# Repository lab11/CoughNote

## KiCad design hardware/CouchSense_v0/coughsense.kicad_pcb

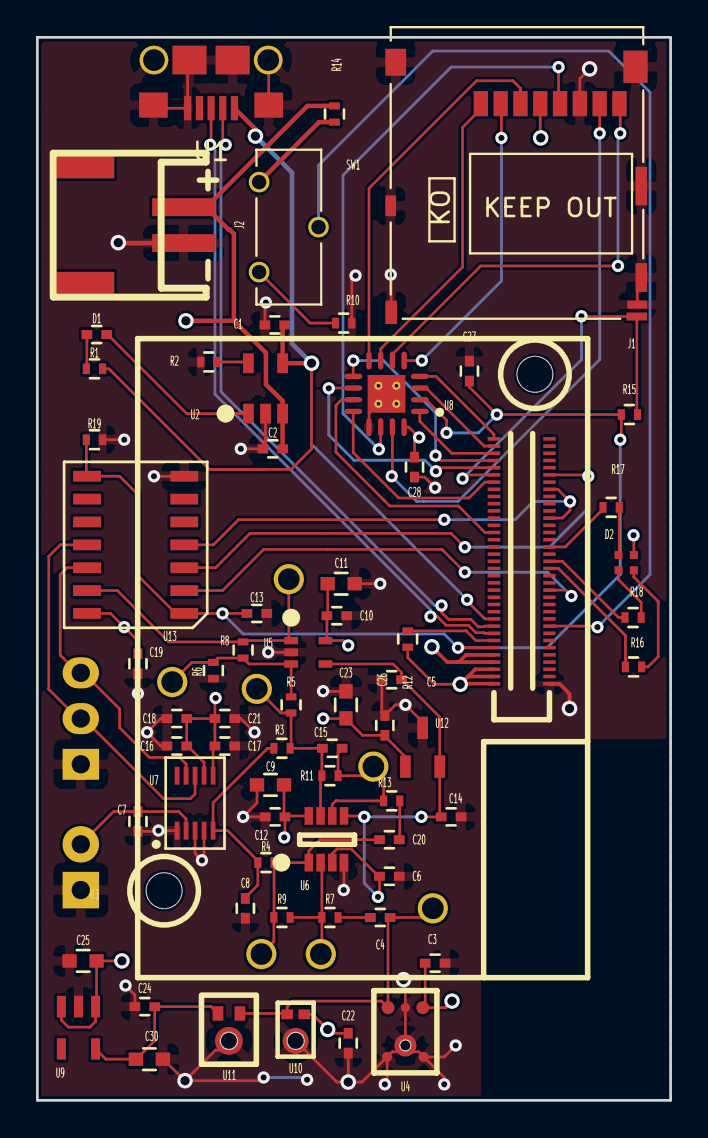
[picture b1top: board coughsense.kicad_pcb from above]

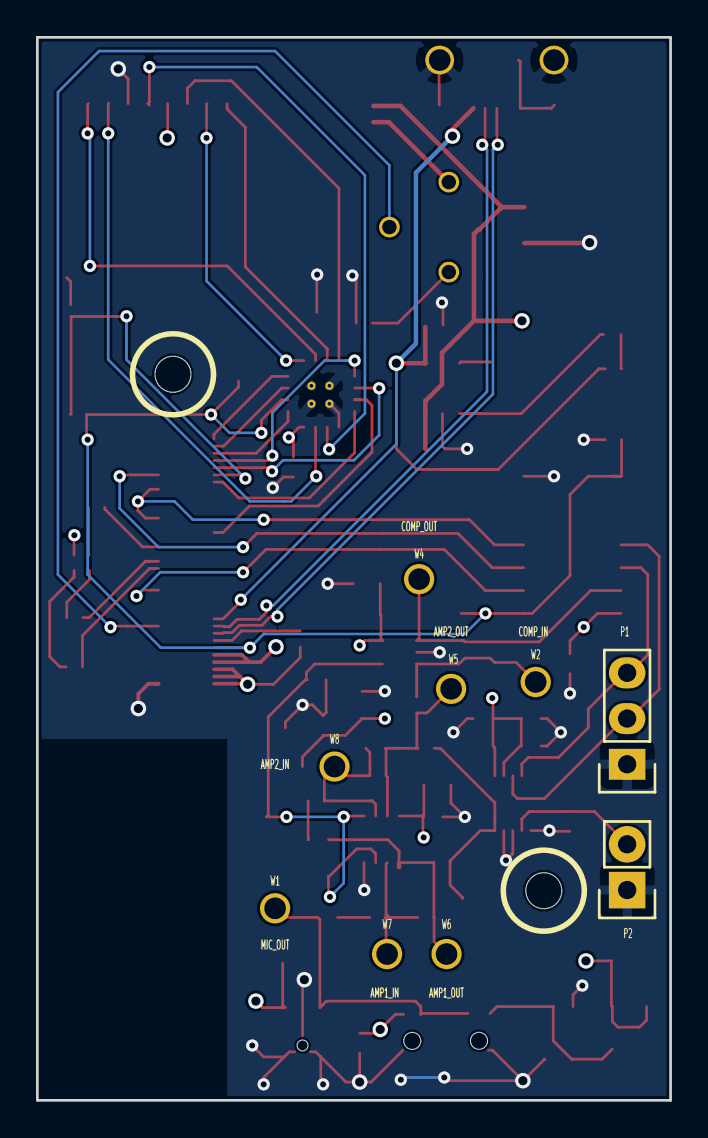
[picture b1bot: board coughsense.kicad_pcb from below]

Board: 4 copper layers, 35.2 x 59.1 mm, 75 parts (8 on the bottom side), 51 nets.

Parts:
C1, C2: C_4.7u_0402_10V_10%_X5R; C_0402
C3, C4, C5, C6, C7, C8, C10, C12, C13, C14, C16, C17, C19, C22, C24, C26, C27, C28: C_0.1u_0402_10V_10%_JB; C_0402
C9, C11, C23: C_10u_0603_10V_10%_JB; C_0603
C15, C20: C_47p_0402_1%_C0G,NP0; C_0402
C18, C21: C_2.2u_0402_10V_10%_JB; C_0402
C25, C30: C_1u_0402_10V_10%_JB; C_0603
D1: LED_GREEN_0402_20mA; C_0402
D2: LED_RGB_0404_10mA; 0404
J1: MicroSD; 2201778-1
J2: JST_2_CONN_SIDE; CONN_JST-2_SMD_SIDE
P1: CONN_01X03; Pin_Header_Straight_1x03
P2: CONN_01X02; Pin_Header_Straight_1x02
R1: R_1K_0402_1%,100ppm/c,0.2W; R_0402
R2: R_2K_0402_1%,100ppm/c,0.1W; R_0402
R3, R4, R5, R6, R8, R12: R_0_0402_.1W; R_0402
R7, R9, R19: R_100K_0402_0.5%,25ppm/c,0.063W; R_0402
R10, R15: R_10k_0402_1%,100ppm/c,0.063W; R_0402
R11, R13: R_220K_0402_1%,100ppm/c,0.063W; R_0402
R14: R_200_0402_1%,100ppm/c,0.1W; R_0402
R16: R_240_0402_1%,100ppm/c,0.063W; R_0402
R17: R_40.2_0402_1%,100ppm/c,0.063W; R_0402
R18: R_60.4_0402_1%,100ppm/c,0.1W; R_0402
SW1: CL-SB_13C; CL-SB-12C
U1: microUSB-B; MICRO_USB_RECEPTABLE
U2: MCP73831T-2ACI/OT; SOT-23-5
U3: edison_iot_module; intel_edison_compute_module
U4: SPU0410LR5H-QB
U5: TS881; SC-70-5
U6: MIC863; SOT-23-8
U7: MAX11205; uSOP-10
U8: MAX13035E; TQFN-16-4x4mm
U9: ADP160AUJZ-1.2-R7; TSOT-5
U10: SPV1840LR5H-B
U11: ICS-40310
U12: ISL60002CIH312Z-TK; ISL60002
U13: TXB0104; SOIC-14
W1, W2, W4, W5, W6, W7, W8: TEST_1P; Testpoint

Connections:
+1V2: C24.1, C30.1, U9.5, U11.3
+1V8: C13.1, C27.1, R15.1, R19.2, U3.12, U8.2, U13.1, U13.8
+BATT: C2.1, J2.1, R12.2, R14.2, U2.3, U3.2, U3.4, U3.6
/ADC_RDY: P1.2, U7.8, U13.11
/ADC_SCLK: P1.3, U7.9, U13.12
/COMP_OUT: R8.2, U5.1, U13.13, W4.1
/D+: U1.3, U3.16
/D-: U1.2, U3.18
/DCIN: R12.1, U3.14
/EDISON_LED_B: R18.2, U3.35
/EDISON_LED_G: R17.2, U3.39
/EDISON_LED_R: R16.2, U3.33
/EDISON_SD_CD: J1.9, R15.2, U3.60
/EDISON_SD_CLK: U3.58, U8.12
/EDISON_SD_CLK_FB: U3.44, U8.11
/EDISON_SD_CMD: U3.62, U8.10
/EDISON_SD_DAT0: U3.66, U8.1
/EDISON_SD_DAT1: U3.70, U8.4
/EDISON_SD_DAT2: U3.64, U8.9
/EDISON_SD_DAT3: U3.68, U8.3
/EDI_ADC_RDY: U3.47, U3.55, U13.4
/EDI_ADC_SCLK: U3.59, U13.3
/EDI_COMP_OUT: U3.27, U13.2
/LED_B: D2.3, R18.1
/LED_G: D2.4, R17.1
/LED_R: D2.2, R16.1
/PWRBTN: SW1.C, U3.17
/SD_CLK: J1.5, U8.14
/SD_CMD: J1.3, U8.8
/SD_DAT0: J1.7, U8.15
/SD_DAT1: J1.8, U8.6
/SD_DAT2: J1.1, U8.7
/SD_DAT3: J1.2, U8.5
/SPU0410LR5H/ADC_IN: C8.1, R3.2, R4.1, U7.5
/SPU0410LR5H/COMP_IN: R5.2, R6.1, R8.1, U5.3, W2.1
/SPU0410LR5H/MIC_AMP1_IN: R7.2, R9.1, U6.2, W7.1
/SPU0410LR5H/MIC_AMP1_OUT: C20.1, R4.2, R9.2, U6.1, W6.1
/SPU0410LR5H/MIC_AMP2_IN: C15.1, R11.2, R13.1, U6.6, W8.1
/SPU0410LR5H/MIC_AMP2_OUT: C15.2, R3.1, R5.1, R11.1, U6.7, W5.1
/SPU0410LR5H/MIC_OUT: C4.2, U4.1, U10.2, U11.1, W1.1
/SPU0410LR5H/VREF: C5.1, C6.1, C14.1, U5.4, U6.3, U6.5, U12.2
/VBUS: C1.1, R1.1, U1.1, U2.4, U3.20
GND: C1.2, C2.2, C3.1, C5.2, C6.2, C7.2, C8.2, C9.2, C10.2, C11.2, C12.2, C13.2, C14.2, C16.2, C17.2, C18.2, C19.2, C21.2, C22.2, C23.2, C24.2, C25.2, C26.2, C27.2, C28.2, C30.2, J1.6, J1.10, J1.11, J1.12, J1.13, J1.14, J1.15, J1.16, J2.2, P1.1, P2.1, R2.2, R6.2, R10.2, R19.1, U1.5, U1.6, U2.2, U3.1, U4.2, U4.3, U4.5, U4.6, U5.2, U6.4, U7.1, U7.3, U7.4, U8.13, U8.17, U9.2, U10.3, U11.2, U12.3, U13.7
unnamed: C4.1, R7.1
unnamed: C20.2, R13.2
unnamed: D1.1, R1.2
unnamed: D1.2, U2.1
unnamed: R2.1, U2.5
unnamed: R10.1, SW1.1
unnamed: R14.1, SW1.2
VCC: C3.2, C7.1, C9.1, C10.1, C11.1, C12.1, C16.1, C17.1, C18.1, C19.1, C21.1, C22.1, C23.1, C25.1, C26.1, C28.1, D2.1, J1.4, P2.2, U3.8, U3.10, U4.4, U5.5, U6.8, U7.2, U7.6, U7.7, U8.16, U9.1, U9.3, U10.1, U12.1, U13.14

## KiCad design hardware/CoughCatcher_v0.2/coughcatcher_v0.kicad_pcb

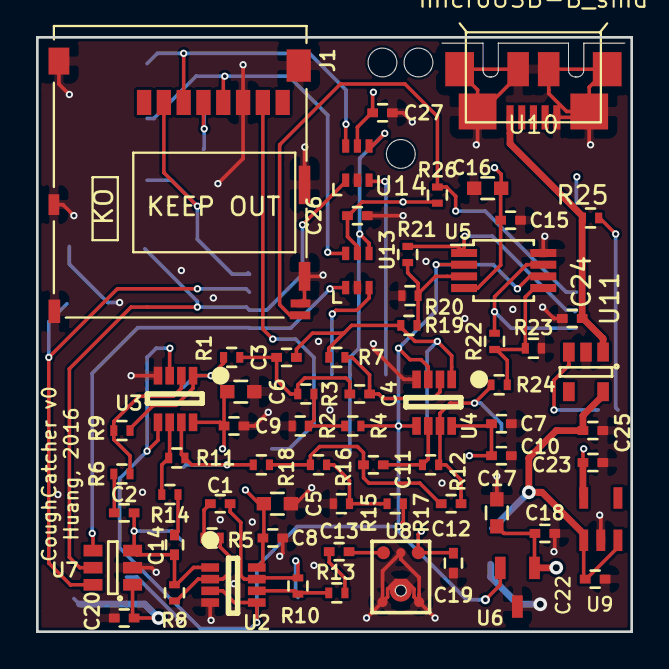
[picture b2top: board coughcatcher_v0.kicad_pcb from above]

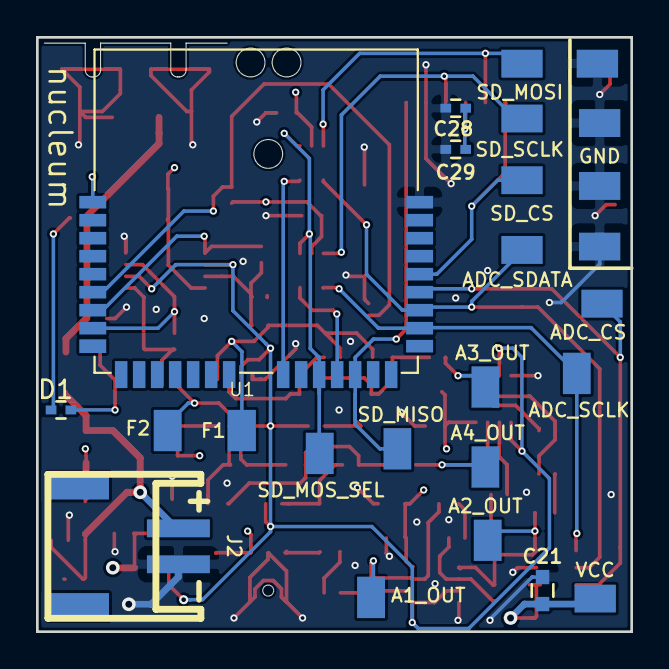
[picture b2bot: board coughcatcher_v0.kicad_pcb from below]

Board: 4 copper layers, 33.0 x 33.0 mm, 90 parts (25 on the bottom side), 43 nets.

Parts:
C1, C2, C7, C8, C9, C13, C14, C15, C18, C19, C20, C22, C23, C26, C27: C_0.1u_0402_10V_10%_JB; C_0402
C3, C4, C11, C12, C24, C25, C28, C29: GENERIC_C_0402; C_0402
C5, C6, C16, C17: C_10u_0603_10V_10%_JB; C_0603
C10: C_4.7u_0402_10V_10%_X5R; C_0402
C21: C_10u_0603_10V_tantalum; C_0603
D1: LED_GREEN_0402_20mA; C_0402
J1: MicroSD; 2201778-1
J2: JST_2_CONN_SIDE; CONN_JST-2_SMD_SIDE
R1, R2, R3, R4, R5, R6, R7, R8, R9, R10, R11, R12, R13, R14, R15, R16, R17, R18, R19, R20, R21, R22, R23, R24, R25, R26: GENERIC_R_0402; R_0402
T1, T3, T4, T5, T6, T7, T8, T9, T10, T11, T12, T13, T14, T17, T18, T19, T20, T21, T22: PROBEPAD_0805
U1: nucleum; NUCLEUM
U2, U3: MIC863; SOT-23-8
U4: MAX9912; SOT-23-8
U5: TS882; MSOP-8_3x3mm_Pitch0.65mm
U6: ISL60002CIH312Z-TK; ISL60002
U7: AD7680; SOT-23-6
U8: SPU0410LR5H-QB
U9: ADP160AUJZ-1.2-R7; TSOT-5
U10: microUSB-B_smd; USB_MICRO_B-HIROSE-ZX62R-B-5P
U11: MAX1555; SOT-23-5
U13, U14: SN74AUP1T157; SC-70-6

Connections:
+3V3: C5.1, C6.1, C7.1, C8.1, C9.1, C10.1, C15.1, C16.1, C17.1, C18.1, C19.1, C20.1, C21.1, C23.1, C26.1, C27.1, C28.1, C29.1, J1.4, R26.1, T1.1, U1.1, U2.8, U3.8, U4.8, U5.4, U6.1, U7.1, U8.4, U9.5, U13.5, U14.5
/BATT: C22.1, C25.1, J2.1, U9.1, U9.3, U11.5
/VBUS: C24.1, R25.2, U10.1, U11.1
ADC_CS: T12.1, U1.27, U7.6
ADC_SCLK: T14.1, U1.25, U7.4, U13.1
ADC_SDATA: T13.1, U1.26, U7.5, U14.1
AMP1_OUT: C1.2, R10.1, T20.1, U2.7
AMP2_OUT: C2.2, C14.1, R8.2, T17.1, U2.1, U7.3
AMP3_OUT: R1.1, R9.2, T18.1, U3.1
AMP4_OUT: R11.1, R18.2, T21.1, U3.7
COMP1_OUT: R21.2, U1.7, U5.1
COMP2_OUT: R22.1, U1.8, U5.7
FILT1_OUT: C3.2, R7.1, R19.1, T19.1, U4.1
FILT2_OUT: C12.1, R12.2, R24.2, T22.1, U4.7
GND: C5.2, C6.2, C7.2, C8.2, C9.2, C10.2, C15.2, C16.2, C17.2, C18.2, C19.2, C20.2, C21.2, C22.2, C23.2, C24.2, C25.2, C26.2, C27.2, C28.2, C29.2, J1.6, J1.10, J1.11, J1.12, J1.13, J1.14, J1.15, J1.16, J2.2, R2.1, R15.1, R20.2, R23.1, T3.1, T4.1, T6.1, T8.1, U1.32, U2.4, U3.4, U4.4, U5.8, U6.3, U7.2, U8.2, U8.3, U8.5, U8.6, U9.2, U10.5, U10.6, U11.2, U13.2, U14.2
MIC_OUT: C13.1, U8.1
unnamed: C1.1, R5.1
unnamed: C2.1, R6.1
unnamed: C3.1, C4.2, R1.2, R3.1
unnamed: C4.1, R7.2, U4.2
unnamed: C11.1, C12.2, R16.1, R18.1
unnamed: C11.2, R12.1, U4.6
unnamed: C13.2, R13.2
unnamed: C14.2, R14.2
unnamed: D1.1, R25.1
unnamed: D1.2, U11.3
unnamed: R2.2, R3.2, R4.1
unnamed: R5.2, R8.1, U2.2
unnamed: R6.2, R9.1, U3.2
unnamed: R10.2, R13.1, U2.6
unnamed: R11.2, R14.1, U3.6
unnamed: R15.2, R16.2, R17.1
unnamed: R19.2, R20.1, R21.1, U5.3
unnamed: R22.2, R23.2, R24.1, U5.5
SD_CS: J1.2, T11.1, U1.28
SD_DET: J1.9, R26.2, U1.6
SD_MISO: J1.7, T10.1, U1.21
SD_MOSI: J1.3, T5.1, U14.6
SD_MOSI_2: U1.17, U14.3
SD_MOSI_SEL: T7.1, U1.19, U13.4, U14.4
SD_SCLK: J1.5, T9.1, U13.6
SD_SCLK_2: U1.20, U13.3
Vref: R4.2, R17.2, U2.3, U2.5, U3.3, U3.5, U4.3, U4.5, U5.2, U5.6, U6.2

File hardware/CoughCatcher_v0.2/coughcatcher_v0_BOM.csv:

"Source:","/home/wwhuang/Dropbox/git/CoughSense/hardware/CoughCatcher_v0.2/coughcatcher_v0.sch"
"Date:","Wed 06 Jul 2016 07:03:46 PM EDT"
"Tool:","Eeschema 4.0.2+dfsg1-stable"
"Component Count:","90"
"Refs","Value","Qty","Vendor 1","Vendor 1 Part Number","Bought"
"C1 C2 C7 C8 C9 C13 C14 C15 C18 C19 C20 C22 C23 C26 C27 ","C_0.1u_0402_10V_10%_JB","15","Digikey","445-10894-1-ND"
"C10 ","C_4.7u_0402_10V_10%_X5R","1","Digikey","445-8023-1-ND"
"C21 ","C_10u_0603_10V_tantalum","1","Digikey","718-1673-1-ND	"
"C3 C4 C11 C12 C24 C25 C28 C29 R1 R2 R3 R4 R5 R6 R7 R8 R9 R10 R11 R12 R13 R14 R15 R16 R17 R18 R19 R20 R21 R22 R23 R24 R25 R26 ","GENERIC_C_0402","34","Digikey","Placeholder"
"C5 C6 C16 C17 ","C_10u_0603_10V_10%_JB","4","Digikey","445-11201-1-ND"
"D1 ","LED_GREEN_0402_20mA","1","Digikey","511-1592-1-ND"
"J1 ","MicroSD","1","Digikey","A118117CT-ND"
"J2 ","JST_2_CONN_SIDE","1","Digikey","455-1749-1-ND"
"T1 T3 T4 T5 T6 T7 T8 T9 T10 T11 T12 T13 T14 T17 T18 T19 T20 T21 T22 ","PROBEPAD_0805","19","Digikey","A106144CT-ND"
"U1 ","nucleum","1","",""
"U10 ","microUSB-B_smd","1","Digikey","H11574CT-ND"
"U11 ","MAX1555","1","Digikey","MAX1555EZK+TCT-ND"
"U13 U14 ","SN74AUP1T157","2","Digikey","296-27393-1-ND"
"U2 U3 ","MIC863","2","Digikey","576-2934-1-ND"
"U4 ","MAX9912","1","Digikey","MAX9912EKA+TCT-ND"
"U5 ","TS882","1","Digikey","497-13800-1-ND"
"U6 ","ISL60002CIH312Z-TK","1","Digikey","ISL60002DIH312Z-TKCT-ND"
"U7 ","AD7680","1","Digikey","	AD7680ARJZ-REEL7CT-ND"
"U8 ","SPU0410LR5H-QB","1","Digikey","423-1139-1-ND"
"U9 ","ADP160AUJZ-1.2-R7","1","Digikey","ADP160AUJZ-1.2-R7CT-ND"

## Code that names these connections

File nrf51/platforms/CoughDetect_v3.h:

#pragma once

#include "spi_master2.h"

#define DUMMY_CS 24

// FRAM chip pins
#define FRAM_CS 12
#define FRAM_MISO    6
#define FRAM_MOSI_2  5
#define FRAM_SCK_2   4
#define FRAM_SPI_SEL 11

//SD Card pins
#define SD_DETECT    21
#define SD_ENABLE    17
#define SD_CS        10
#define SD_MISO      7
#define SD_MOSI      9
#define SD_SCK       8

// ADC pins
#define ADC_CS   3
#define ADC_MISO 2
#define ADC_SCK  13

// Cough pins
#define COMP1 22
#define COMP2 23

// LED pins
#define LED0          18 // red
#define LED1          19 // blue
#define LED2          20 // green
#define LED_RED       LED0
#define LED_BLUE      LED1
#define LED_GREEN     LED2
#define LED_DEBUG     LED1

/* NUCLEUM PINS copied from nucleum.h. Copied so that I could use FRAM for my #defines*/

// This pin is mapped to the FTDI chip to all the device to enter the
// bootloader mode.
#define BOOTLOADER_CTRL_PIN  13
#define BOOTLOADER_CTRL_PULL NRF_GPIO_PIN_PULLUP

#define RX_PIN_NUMBER  11
#define TX_PIN_NUMBER  12
#define CTS_PIN_NUMBER 0
#define RTS_PIN_NUMBER 0
#define HWFC           false

#define NUC_SPI_SCK_PIN     0     /**< SPI clock GPIO pin number. */
#define NUC_SPI_MOSI_PIN    30     /**< SPI Master Out Slave In GPIO pin number. */
#define NUC_SPI_MISO_PIN    29     /**< SPI Master In Slave Out GPIO pin number. */
#define NUC_RV3049_CS		28
#define NUC_RV3049_INT		25
#define NUC_FRAM_HOLD       14
#define NUC_FRAM_CS		    15
#define NUC_FRAM_WP		    16
#define NUC_XL1				46
#define NUC_XL2				45

/* Pins for SD Card */
#define SPI_SCK_PIN     8     /**< SPI clock GPIO pin number. */
#define SPI_MOSI_PIN    9     /**< SPI Master Out Slave In GPIO pin number. */
#define SPI_MISO_PIN    7     /**< SPI Master In Slave Out GPIO pin number. */
#define SPI_CS_PIN		10
#define SD_ENABLE_PIN	17		//power gates sd card
#define CD_PIN			21

/* Various spi configurations defined in CoughDetect_v3.c */
extern SPIConfig_t adc_spi;
extern SPIConfig_t fram_spi;
extern SPIConfig_t sdcard_spi;
extern SPIConfig_t nuc_rtc_spi;

/* This function doesn't initialize functions such as spi, just sets the output/input correctly*/
void configure_platform_pins();

/* Configure fram chip to be hooked up to the nucleum */
void configure_fram_fram();

/* Configure FRAM chip to be shorted to ADC for direct writes */
void configure_fram_adc();

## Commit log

2016-07-29 hardware files
2016-08-17 ignore build files
2016-08-17 software files
2017-01-27 test for sdcard using simple_logger
2017-01-27 platforms for CoughDetect boards
2017-01-27 minor updates
2017-01-29 added nrf5x sub module
2017-01-29 various tests for the CoughDetect v3
2017-01-30 added spi configs to platform files
2017-03-30 cough detector that stores coughs as binary data on sd card
2017-03-30 bugfixes
2017-03-31 changes to ble time sync, node side
2017-03-31 changes to ble time sync, base statoin side. time is super off
2017-03-31 fixed get_unixtime not updating seconds
2017-04-06 app to store unproccessed adc readings to flash
2017-04-06 whitespace changess?
2017-04-06 update submodule pointer
2017-07-25 fixed timer not being initialized
